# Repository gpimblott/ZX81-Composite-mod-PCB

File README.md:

# ZX81-Composite-mod-PCB
PCB that implements the ZX81 composite mod including the backporch signal for older versions 

The PCB KiKad files in this repo implement a composite mod board for the ZX81 as described [here](http://zx.zigg.net/misc-projects/ZX81_Video_Conditioning.pdf).  More details can also be found on the excellent [joulespercoulomb YouTube video](https://www.youtube.com/watch?v=1irH3KuGyl0).

If the backporch signal is not required then the 555 timer chip can be omitted.  I have used this on two ZX81's without the 555 and it results in a much better picture than the frequently described transistor mod alone.

NOTE : This is V2 of the board.  V1 had a small error requiring a patch wire and track to be cut.  I have not yet had v2 manufactured and tested.

# Parts list

The following components are needed to complete the PCB
* R1,R2 - 10K Resistor
* R3 - 68 Resistor
* R4 - 56 Resistor
* C1 - 22uF electrolytic capacitor
* C2 - 10nF ceramic disc capacitor
* C3 - 820pF ceramic disc capacitor
* C4 - 82pF ceramic disc capacitor
* Q1,Q2 - 2N2222 transistor
* D1,D2 - 1N4148 signal diodes
* U1 - NE555 Timer (Optional)

# Fitting the board
The board is redesigned to fit inside the existing housing once the original modulator has been removed.  This is done by desoldering the 5v and video signal wires entering the metal casing from the mother board then desoldering the large casing anchors.  Once this is done you should be able to remove the modulator.  The bottom can then be removed.  Once this is done the ground bridges will need to be desoldered anchoring the PCB into the case.  The signal wire from the PCB to the composite output jack will also need to be desoldered.

Getting it free can be pain and worse if you want to keep the original modulator in one piece.  Once removed the new PCB can be inserted and connected to the necessary locations
* 5v to the motherboard (same as the original)
* Video in to the motherboard (same as the original)
* Video out to the centre of the jack
* Ground to the modulator casing (don't forget to use the underside pads to anchor the PCB into the casing (and earth the PCB)

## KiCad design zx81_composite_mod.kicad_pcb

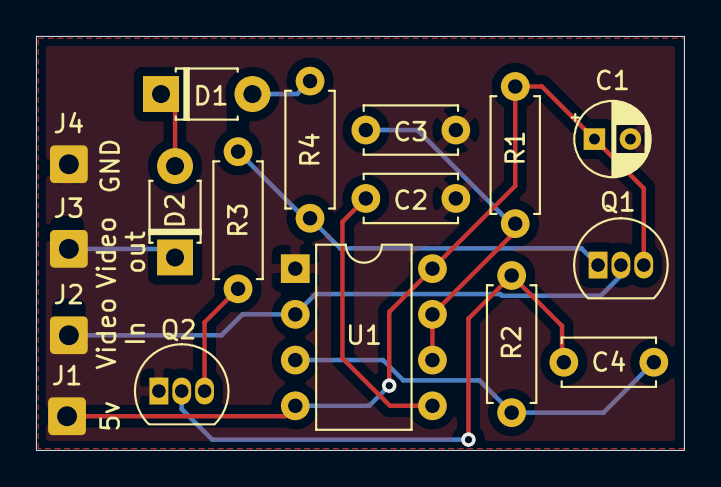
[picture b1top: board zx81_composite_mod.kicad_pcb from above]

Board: 2 copper layers, 36.0 x 23.0 mm, 17 parts (0 on the bottom side), 12 nets.

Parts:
C1: 22uF; CP_Radial_D4.0mm_P2.00mm
C2: 10nF; C_Disc_D5.0mm_W2.5mm_P5.00mm
C3: 820pF; C_Disc_D5.0mm_W2.5mm_P5.00mm
C4: 82pF; C_Disc_D5.0mm_W2.5mm_P5.00mm
D1, D2: 1N4148; D_T-1_P5.08mm_Horizontal
J1: +5v; SolderWire-0.5sqmm_1x01_D0.9mm_OD2.1mm
J2: Video_in; SolderWire-0.5sqmm_1x01_D0.9mm_OD2.1mm
J3: Video_out; SolderWire-0.5sqmm_1x01_D0.9mm_OD2.1mm
J4: GND; SolderWire-0.5sqmm_1x01_D0.9mm_OD2.1mm
Q1, Q2: PN2222A; TO-92_Inline
R1, R2: 10K; R_Axial_DIN0207_L6.3mm_D2.5mm_P7.62mm_Horizontal
R3: 68; R_Axial_DIN0207_L6.3mm_D2.5mm_P7.62mm_Horizontal
R4: 56; R_Axial_DIN0207_L6.3mm_D2.5mm_P7.62mm_Horizontal
U1: NE555P; DIP-8_W7.62mm

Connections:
+5V: C1.1, J1.1, Q1.3, R1.1, U1.4, U1.8
GND: C1.2, C2.2, C3.2, J4.1, Q2.1, U1.1
unnamed: C2.1, U1.5
unnamed: C3.1, R1.2, U1.6, U1.7
unnamed: C4.1, Q2.2, R2.1
unnamed: C4.2, R2.2, U1.3
unnamed: D1.1, D2.2
unnamed: D1.2, R4.2
unnamed: Q1.1, R3.1, R4.1
unnamed: Q2.3, R3.2
Video_in: J2.1, Q1.2, U1.2
Video_out: D2.1, J3.1

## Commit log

2021-11-21 Initial commit of v2 pcb
